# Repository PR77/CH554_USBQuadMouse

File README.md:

# CH554 USB MOUSE + KEYBOARD <-> AMIGA X-LATER
USB MOUSE + KEYBOARD <-> AMIGA X-LATER based on the WCH554 MCS51 based chip with USB Device + Host Interface. 

# Warning
This design has not been compliance tested and will not be. It may cause personal damage to you or others. I take no responsibility for this. I accept no responsibility for any damage to any equipment that results from the use of this design and its components. IT IS ENTIRELY AT YOUR OWN RISK!

# Overview
This project allows you to use a USB mouse or keyboard on an Amiga computer - of course only one-or-the-other is supported at any one time. It essentially converts a USB mouse to generate a quadrature signal stream, similarly it converts a USB keyboard keycodes (currently only DE is implemented) to work with an Amiga. There are many variants of such a project available, either using this micro controller or others, however I'm using this project as an opportunity to learn more about the WCH55x micro controller.

# Appearance Breadboard Version
I forgot to take a picture of the mess of wires breadboard version, so here is a picture on some perf-board instead. I'm using the USB B socket for debugging and the USB A socket is for the Mouse Connection. Of course only 1 device (either PC for debugging or Mouse for using) can be connected. I got the two USB sockets from an old printer board I found lying around the house.

# Appearance Final PCB Version
PCB version has been routed and manufactured for supporting a mouse or keyboard. Here is the usual 3D artwork of the design.

OLED is also supported so you can see some information for example keyboard and mouse report data.

# Credits
I refacted a lot of the original libraries into various software components. However there were some repos which provided me with excellent information, tools and resources;
- https://github.com/wagiminator
- https://github.com/Blinkinlabs/ch554_sdcc
- https://github.com/HonghongLu/CH554

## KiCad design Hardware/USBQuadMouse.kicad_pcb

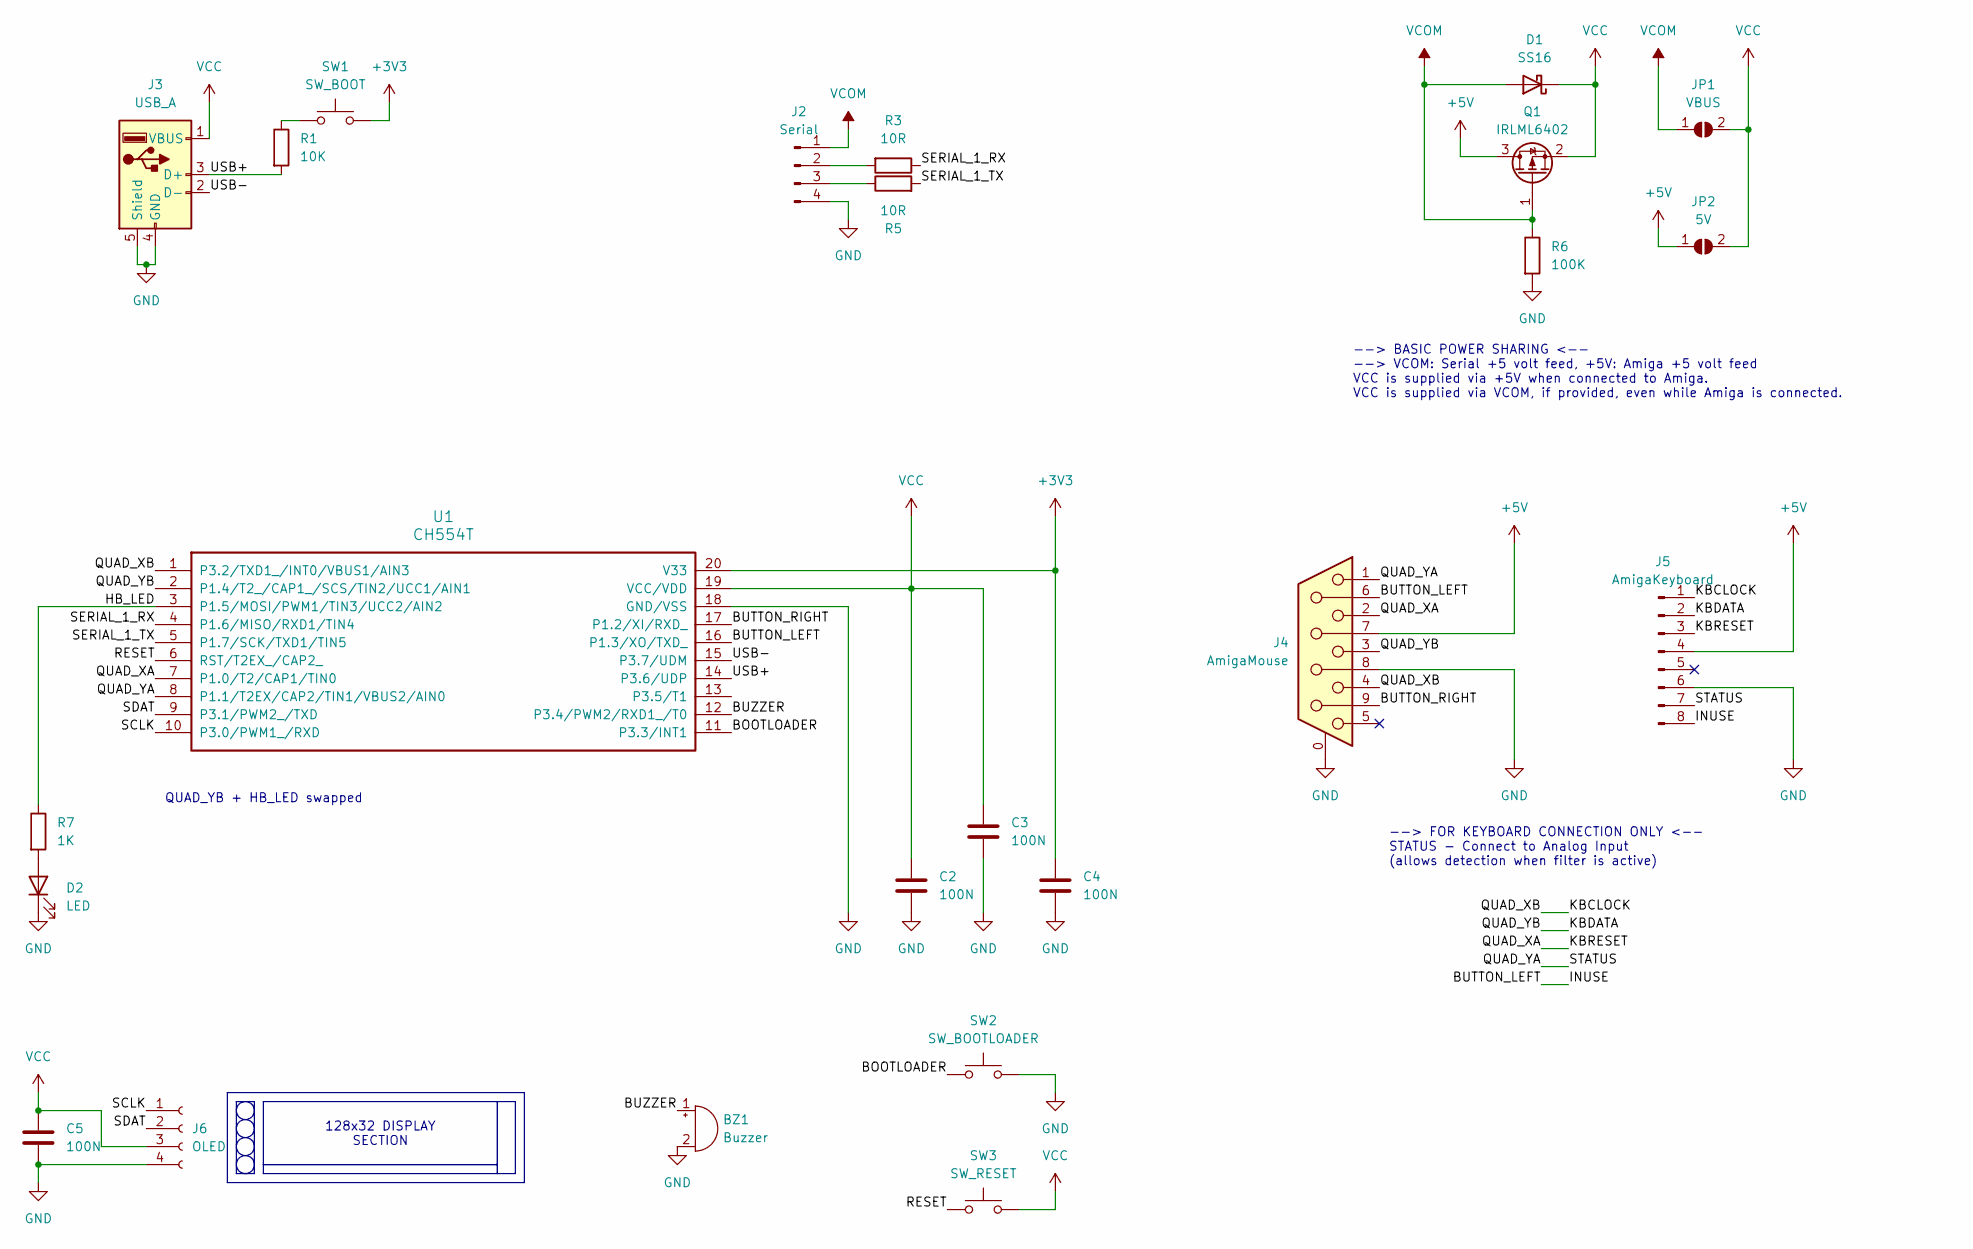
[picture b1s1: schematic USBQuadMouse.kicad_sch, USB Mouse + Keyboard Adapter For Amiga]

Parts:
BZ1: Buzzer; Buzzer_15x7.5RM7.6
C2, C3, C4, C5: 100N; C_0805_2012Metric_Pad1.18x1.45mm_HandSolder
D1: SS16; D_SMA
D2: LED; LED_0805_2012Metric_Pad1.15x1.40mm_HandSolder
J2: Serial; PinHeader_1x04_P2.54mm_Vertical
J3: USB_A; USB_A_Molex_67643_Horizontal
J4: AmigaMouse; DSUB-9_Female_EdgeMount_P2.77mm
J5: AmigaKeyboard; PinHeader_1x08_P2.54mm_Vertical
J6: OLED; PinSocket_1x04_P2.54mm_Vertical
JP1: VBUS; SolderJumper-2_P1.3mm_Open_RoundedPad1.0x1.5mm
JP2: 5V; SolderJumper-2_P1.3mm_Open_RoundedPad1.0x1.5mm
Q1: IRLML6402; SOT-23
R1: 10K; R_0805_2012Metric_Pad1.20x1.40mm_HandSolder
R3, R5: 10R; R_0805_2012Metric_Pad1.20x1.40mm_HandSolder
R6: 100K; R_0805_2012Metric_Pad1.20x1.40mm_HandSolder
R7: 1K; R_0805_2012Metric_Pad1.20x1.40mm_HandSolder
SW1: SW_BOOT; SW_DIP_SPSTx01_Slide_Copal_CHS-01B_W7.62mm_P1.27mm
SW2: SW_BOOTLOADER; SW_DIP_SPSTx01_Slide_Copal_CHS-01B_W7.62mm_P1.27mm
SW3: SW_RESET; SW_DIP_SPSTx01_Slide_Copal_CHS-01B_W7.62mm_P1.27mm
U1: CH554T; TSSOP-20_4.4x6.5mm_P0.65mm; LCSC C2928938

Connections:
+3V3: C4.1, SW1.2, U1.20 (V33)
+5V: J4.7, J5.4, JP2.1 (A), Q1.3 (D)
/BOOTLOADER: SW2.2, U1.11 (P3.3/INT1)
/BUTTON_LEFT: J4.6, J5.8, U1.16 (P1.3/XO/TXD_)
/BUTTON_RIGHT: J4.9, U1.17 (P1.2/XI/RXD_)
/BUZZER: BZ1.1 (-), U1.12 (P3.4/PWM2/RXD1_/T0)
/HB_LED: R7.1, U1.3 (P1.5/MOSI/PWM1/TIN3/UCC2/AIN2)
/KBCLOCK: J4.4, J5.1, U1.1 (P3.2/TXD1_/INT0/VBUS1/AIN3)
/KBDATA: J4.3, J5.2, U1.2 (P1.4/T2_/CAP1_/SCS/TIN2/UCC1/AIN1)
/KBRESET: J4.2, J5.3, U1.7 (P1.0/T2/CAP1/TIN0)
/QUAD_YA: J4.1, J5.7, U1.8 (P1.1/T2EX/CAP2/TIN1/VBUS2/AIN0)
/RESET: SW3.1, U1.6 (RST/T2EX_/CAP2_)
/SCLK: J6.1, U1.10 (P3.0/PWM1_/RXD)
/SDAT: J6.2, U1.9 (P3.1/PWM2_/TXD)
/SERIAL_1_RX: R3.1, U1.4 (P1.6/MISO/RXD1/TIN4)
/SERIAL_1_TX: R5.2, U1.5 (P1.7/SCK/TXD1/TIN5)
/USB+: J3.3 (D+), R1.2, U1.14 (P3.6/UDP)
/USB-: J3.2 (D-), U1.15 (P3.7/UDM)
GND: BZ1.2 (+), C2.2, C3.2, C4.2, C5.2, D2.1 (K), J2.4, J3.4 (GND), J3.5 (Shield), J4.0 (PAD), J4.8, J5.6, J6.4, R6.2, SW2.1, U1.18 (GND/VSS)
unnamed: D2.2 (A), R7.2
unnamed: J2.2, R3.2
unnamed: J2.3, R5.1
unnamed: R1.1, SW1.1
VCC: C2.1, C3.1, C5.1, D1.1 (K), J3.1 (VBUS), J6.3, JP1.2 (B), JP2.2 (B), Q1.2 (S), SW3.2, U1.19 (VCC/VDD)
VCOM: D1.2 (A), J2.1, JP1.1 (A), Q1.1 (G), R6.1

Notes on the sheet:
128x32 DISPLAY SECTION
--> BASIC POWER SHARING <-- --> VCOM: Serial +5 volt feed, +5V: Amiga +5 volt feed VCC is supplied via +5V when connected to Amiga. VCC is supplied via VCOM, if provided, even while Amiga is connected.
QUAD_YB + HB_LED swapped
--> FOR KEYBOARD CONNECTION ONLY <-- STATUS - Connect to Analog Input (allows detection when filter is active)

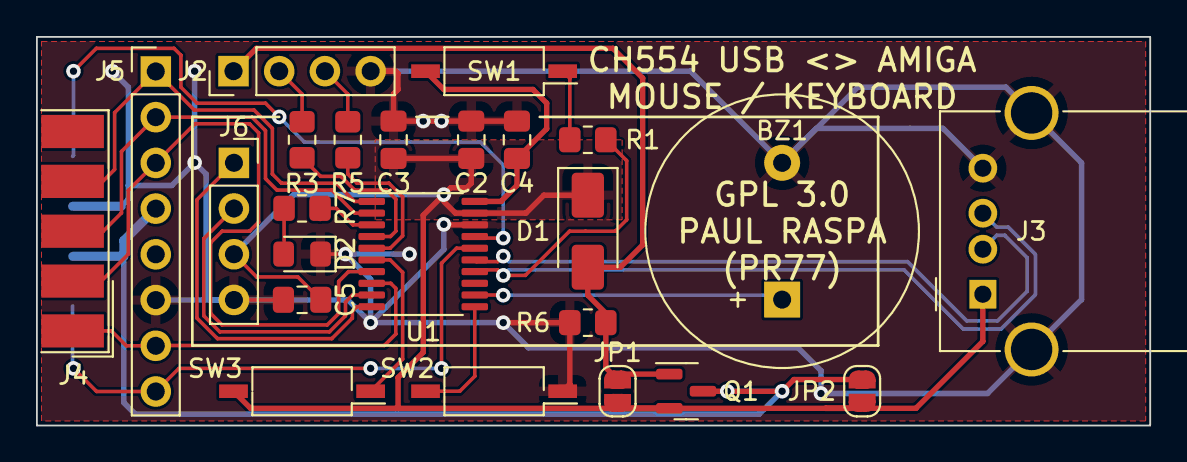
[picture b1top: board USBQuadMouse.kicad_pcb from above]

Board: 2 copper layers, 61.8 x 21.6 mm, 24 parts (0 on the bottom side), 25 nets.

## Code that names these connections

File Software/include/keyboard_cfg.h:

/********************************** (C) COPYRIGHT *******************************
* File Name     : KEYBOARD_CFG.H
* Author        : Paul Raspa (PR77)
* License       : MIT
* Version       : V1.0
* Date          : 2025/10/23
* Description   : CH554 Amiga Keyboard Emulation
*******************************************************************************/

#ifndef __CH554_KEYBOARD_CFG_H__
#define __CH554_KEYBOARD_CFG_H__

#include <stdint.h>
#include "ch554.h"

#ifndef KBCLOCK_PORT
#define KBCLOCK_PORT        0xB0
#endif

#ifndef KBCLOCK_MOD_OC
#define KBCLOCK_MOD_OC      P3_MOD_OC
#endif

#ifndef KBCLOCK_DIR_PU
#define KBCLOCK_DIR_PU      P3_DIR_PU
#endif

#ifndef KBCLOCK_PIN
#define KBCLOCK_PIN         2
#endif

#ifndef KBDATA_PORT
#define KBDATA_PORT         0x90
#endif

#ifndef KBDATA_MOD_OC
#define KBDATA_MOD_OC       P1_MOD_OC
#endif

#ifndef KBDATA_DIR_PU
#define KBDATA_DIR_PU       P1_DIR_PU
#endif

#ifndef KBDATA_PIN
#define KBDATA_PIN          4
#endif

#ifndef KBRESET_PORT
#define KBRESET_PORT        0x90
#endif

#ifndef KBRESET_MOD_OC
#define KBRESET_MOD_OC      P1_MOD_OC
#endif

#ifndef KBRESET_DIR_PU
#define KBRESET_DIR_PU      P1_DIR_PU
#endif

#ifndef KBRESET_PIN
#define KBRESET_PIN         0
#endif

#ifndef KBSTATUS_PORT
#define KBSTATUS_PORT       0x90
#endif

#ifndef KBSTATUS_MOD_OC
#define KBSTATUS_MOD_OC     P1_MOD_OC
#endif

#ifndef KBSTATUS_DIR_PU
#define KBSTATUS_DIR_PU     P1_DIR_PU
#endif

#ifndef KBSTATUS_PIN
#define KBSTATUS_PIN        1
#endif

#ifndef KBINUSE_PORT
#define KBINUSE_PORT        0x90
#endif

#ifndef KBINUSE_MOD_OC
#define KBINUSE_MOD_OC      P1_MOD_OC
#endif

#ifndef KBINUSE_DIR_PU
#define KBINUSE_DIR_PU      P1_DIR_PU
#endif

#ifndef KBINUSE_PIN
#define KBINUSE_PIN         3
#endif

#endif // __CH554_KEYBOARD_CFG_H__

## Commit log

2024-12-17 Updates
    Improvements and starting to add Serial 1 functions.
2025-03-16 Updates
    Quadrature encoder still in development. Will link the execution of the sequencer to Timer 2 interrupt.
2025-03-27 Updates
    Added support for Serial Port 1 transmit interrupts. More to come.
2025-03-28 Updates
    Receive interrupt added, still be debugged.
2025-03-31 Updates
    Fixed #ifdefs to enable or disable TX and RX interrupts.
2025-04-09 Updates + WIP
    Updates to Serial Driver and WIP on Quadrature Encoder interrupt handler.
2025-05-17 Updates
    Changed pin allocations for prototype board layout.
2025-05-20 Updates
    Updates for prototype board and added buzzer support.
2025-05-21 Updates
    Fixed buzzer routines.
2025-05-21 Updates
    Thanks to "wagiminator" references for setting PWM frequency macro.
2025-05-22 Updates
    Added some usability fixes.
2025-05-22 Updates
    Added images.
2025-05-22 Updates
    Updated folder structure.
2025-05-22 Updates
    Added some documents.
2025-10-09 Updates
    Prep work for PCB version.
2025-10-23 Updates
    Added PCB and framework for Amiga Keyboard emulation.
2025-11-02 Updates
    Major refactor and continued support for keyboard.
2025-11-03 Updates
    Fixed some F_CPU / FREQ_SYS macro related issues and improved Serial 1 TX interrupt handler.
2025-11-05 Updates
    Added support to switch automatically between Keyboard or Mouse based on what is connected.
2025-11-09 Updates
    Code cleanup improved keyboard (and mouse) support.
2025-11-09 Updates
    Better show if a Keyboard or Mouse has been connected.
2025-11-10 Updates
    Added some NULL pointer checks.
2025-11-17 Updates
    Tuning to keyboard timing.
2025-11-19 Updates
    Added a queue to key codes being sent to Amiga.
2025-11-20 Updates
    Fixed a nasty bug what would not handle the USB keyboard changing the order of the report content.
2025-11-21 Updates
    A couple of bug fixes.
2025-11-21 Updates
    Keyboard support is now done.
2025-11-29 Updates
    Some code quality updates and fixed an annoying bug where the Y Axis would sometime changes direction.
2025-11-30 Updates
    Made some improvements to reduce the lag.

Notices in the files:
Hardware/USBQuadMouse.kicad_pcb:
GPL 3.0
